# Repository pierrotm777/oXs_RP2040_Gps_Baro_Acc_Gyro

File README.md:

# oXs_RP2040_Gps_Baro_Acc_Gyro
 Multi Telemetry Protocols RP2040 Full version
 
## PCBWAY board link
You can find my shared pcb project [here](https://www.pcbway.com/project/shareproject/oXs_RP2040_Full_fdfb35e8.html).

 <object data="http://yoursite.com/the.pdf" type="application/pdf" width="700px" height="700px">
    <embed src="http://yoursite.com/the.pdf">
        <p>This browser does not support PDFs. Please download the PDF to view it: <a href="http://yoursite.com/the.pdf">Download PDF</a>.</p>
    </embed>
</object>

xfun::embed_file("homework.pdf")

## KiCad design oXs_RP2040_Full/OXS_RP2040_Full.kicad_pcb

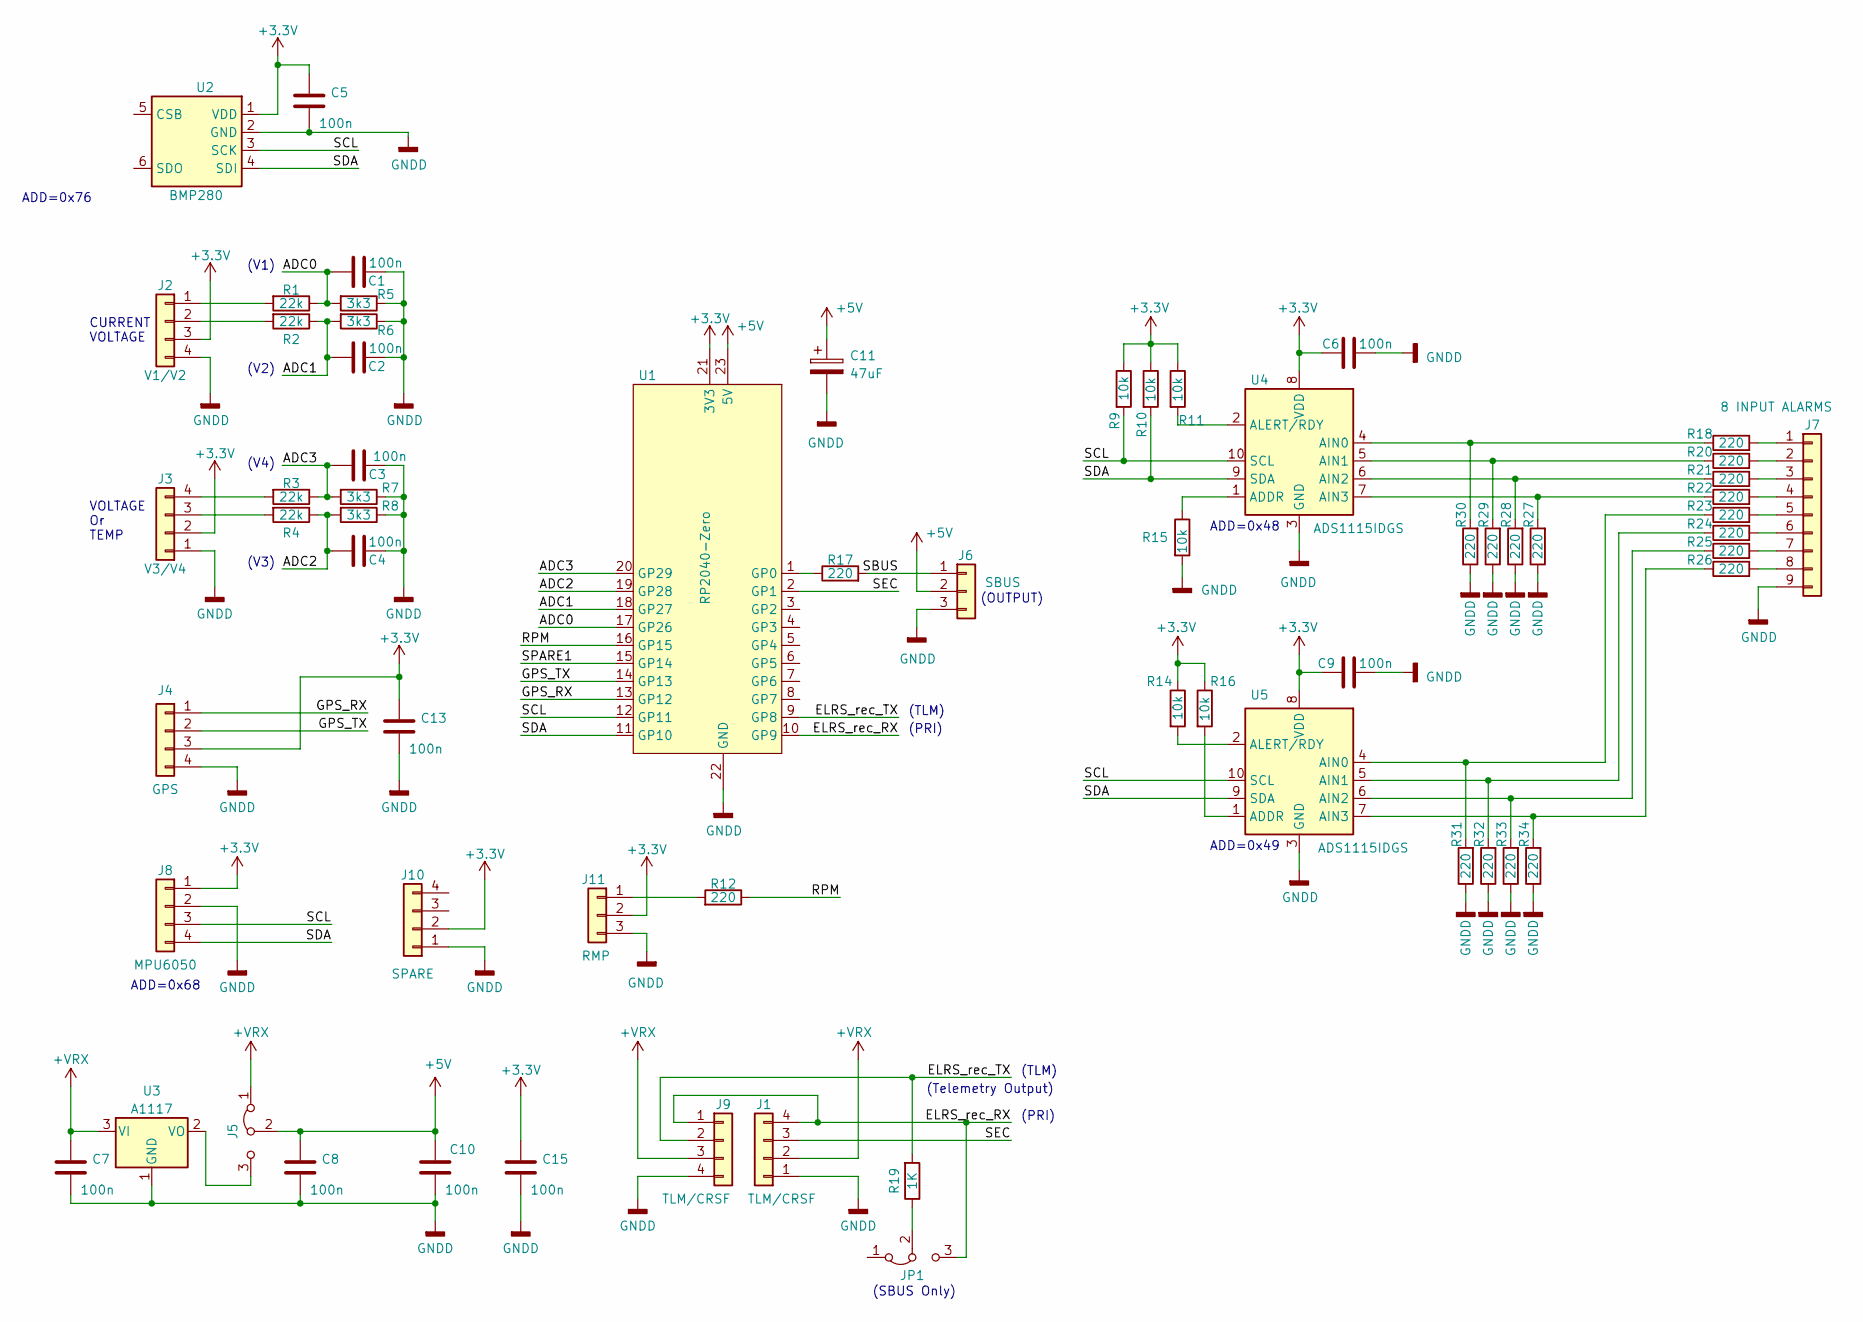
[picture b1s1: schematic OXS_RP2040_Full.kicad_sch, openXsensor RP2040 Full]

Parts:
C1, C2, C3, C4, C5, C6, C7, C8, C9, C10, C13, C15: 100n; C_1206_3216Metric_Pad1.33x1.80mm_HandSolder
C11: 47uF; CAPPM7343X310N
J1, J9: TLM/CRSF; PinHeader_1x04_P2.54mm_Horizontal_Mod
J2: V1/V2; PinHeader_1x04_P2.54mm_Horizontal_Mod
J3: V3/V4; PinHeader_1x04_P2.54mm_Horizontal_Mod
J4: GPS; PinHeader_1x04_P2.54mm_Horizontal_Mod
J5: SELECT_POWER; PinHeader_1x03_P2.54mm_Vertical
J6: SBUS; Pin_Header_Straight_1x03_Mod_Pitch2.54mm
J7: 8 INPUT ALARMS; JST_EH_B9B-EH-A_1x09_P2.50mm_Vertical
J8: MPU6050; PinHeader_1x04_P2.54mm_Vertical
J10: SPARE; PinHeader_1x04_P2.54mm_Horizontal_Mod
J11: RMP; Pin_Header_Straight_1x03_Mod_Pitch2.54mm
JP1: SBUS2; PinHeader_1x03_P2.54mm_Vertical
R1, R2, R3, R4: 22k; R_1206_3216Metric_Pad1.30x1.75mm_HandSolder
R5, R6, R7, R8: 3k3; R_1206_3216Metric_Pad1.30x1.75mm_HandSolder
R9, R10, R11, R14, R15, R16: 10k; R_1206_3216Metric_Pad1.30x1.75mm_HandSolder
R12, R17, R18, R20, R21, R22, R23, R24, R25, R26, R27, R28, R29, R30, R31, R32, R33, R34: 220; R_1206_3216Metric_Pad1.30x1.75mm_HandSolder
R19: 1K; R_1206_3216Metric_Pad1.30x1.75mm_HandSolder
U1: RP2040-Zero
U2: BMP280
U3: A1117; SOT-223-3_TabPin2
U4, U5: ADS1115IDGS; TSSOP-10_3x3mm_P0.5mm

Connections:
+3.3V: C5.1, C6.2, C9.2, C13.1, C15.1, J2.3, J3.2, J4.3, J8.1, J10.2, J11.2, R9.1, R10.1, R11.1, R14.1, R16.1, U1.21 (3V3), U2.1 (VDD), U4.8 (VDD), U5.8 (VDD)
+5V: C8.1, C10.1, C11.1, J5.2 (C), J6.2, U1.23 (5V)
+VRX: C7.1, J1.2, J5.1 (A), J9.3, U3.3 (VI)
/ADC0: C1.2, R1.1, R5.2, U1.17 (GP26)
/ADC1: C2.2, R2.1, R6.2, U1.18 (GP27)
/ADC2: C4.2, R4.1, R8.2, U1.19 (GP28)
/ADC3: C3.2, R3.1, R7.2, U1.20 (GP29)
/ELRS_rec_RX: J1.4, J9.1, JP1.3 (B), U1.10 (GP9)
/ELRS_rec_TX: J9.2, R19.2, U1.9 (GP8)
/GPS_RX: J4.1, U1.13 (GP12)
/GPS_TX: J4.2, U1.14 (GP13)
/RPM: R12.1, U1.16 (GP15)
/SBUS: J6.1, R17.2
/SCL: J8.3, R9.2, U1.12 (GP11), U2.3 (SCK), U4.10 (SCL), U5.10 (SCL)
/SDA: J8.4, R10.2, U1.11 (GP10), U2.4 (SDI), U4.9 (SDA), U5.9 (SDA)
/SEC: J1.3, U1.2 (GP1)
/SPARE1: U1.15 (GP14)
GNDD: C1.1, C2.1, C3.1, C4.1, C5.2, C6.1, C7.2, C8.2, C9.1, C10.2, C11.2, C13.2, C15.2, J1.1, J2.4, J3.1, J4.4, J6.3, J7.9, J8.2, J9.4, J10.1, J11.3, R5.1, R6.1, R7.1, R8.1, R15.2, R27.1, R28.1, R29.1, R30.1, R31.1, R32.1, R33.1, R34.1, U1.22 (GND), U2.2 (GND), U3.1 (GND), U4.3 (GND), U5.3 (GND)
unnamed: J2.1, R1.2
unnamed: J2.2, R2.2
unnamed: J3.3, R4.2
unnamed: J3.4, R3.2
unnamed: J5.3 (B), U3.2 (VO)
unnamed: J7.1, R18.2
unnamed: J7.2, R20.2
unnamed: J7.3, R21.2
unnamed: J7.4, R22.2
unnamed: J7.5, R23.2
unnamed: J7.6, R24.2
unnamed: J7.7, R25.2
unnamed: J7.8, R26.2
unnamed: J11.1, R12.2
unnamed: JP1.2 (C), R19.1
unnamed: R17.1, U1.1 (GP0)
unnamed: R15.1, U4.1 (ADDR)
unnamed: R18.1, R30.2, U4.4 (AIN0)
unnamed: R20.1, R29.2, U4.5 (AIN1)
unnamed: R21.1, R28.2, U4.6 (AIN2)
unnamed: R22.1, R27.2, U4.7 (AIN3)
unnamed: R11.2, U4.2 (ALERT/RDY)
unnamed: R16.2, U5.1 (ADDR)
unnamed: R23.1, R31.2, U5.4 (AIN0)
unnamed: R24.1, R32.2, U5.5 (AIN1)
unnamed: R25.1, R33.2, U5.6 (AIN2)
unnamed: R26.1, R34.2, U5.7 (AIN3)
unnamed: R14.2, U5.2 (ALERT/RDY)

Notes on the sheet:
CURRENT VOLTAGE
(SBUS Only)
(V4)
ADD=0x49
(TLM)
(PRI)
(V2)
VOLTAGE Or TEMP
(OUTPUT)
(V1)
ADD=0x48
(Telemetry Output)
ADD=0x76
(V3)
ADD=0x68

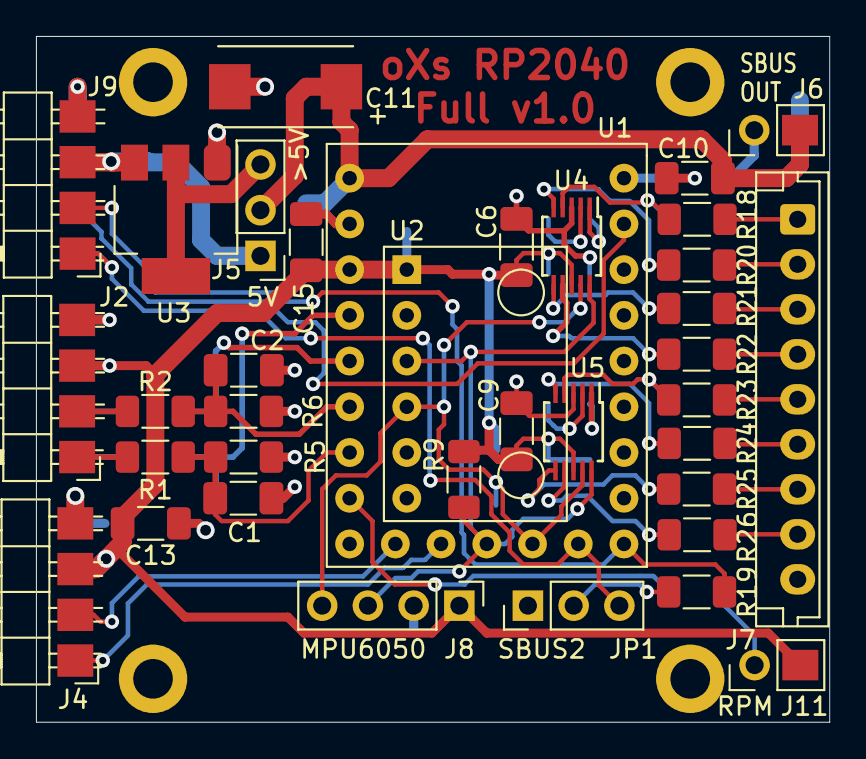
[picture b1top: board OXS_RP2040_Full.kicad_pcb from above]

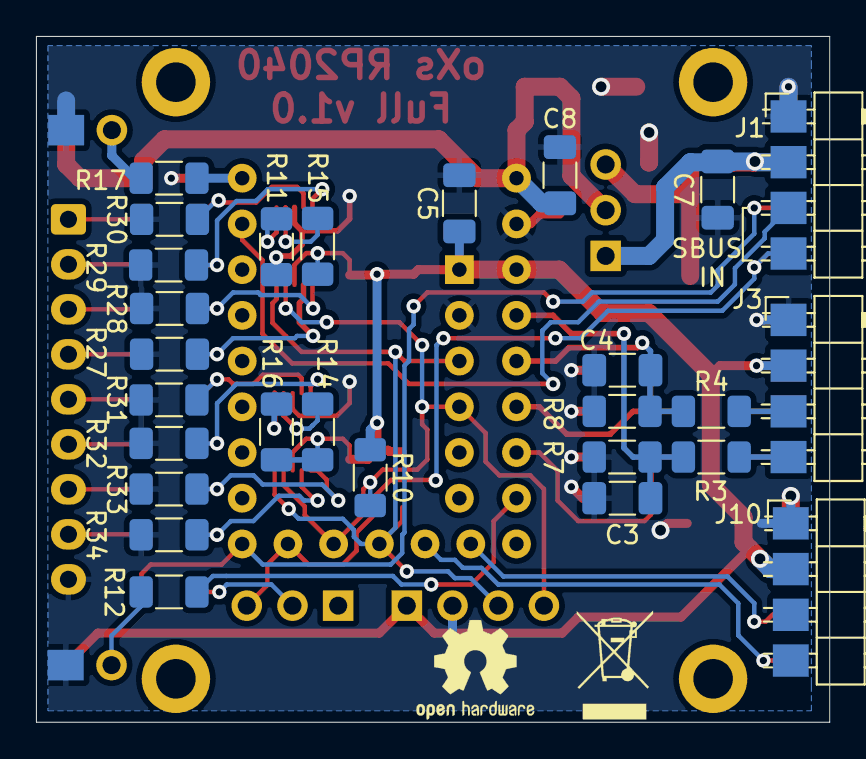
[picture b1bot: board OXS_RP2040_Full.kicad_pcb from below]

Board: 2 copper layers, 44.1 x 38.1 mm, 63 parts (27 on the bottom side), 45 nets.

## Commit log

2023-03-28 Add Kicad files & Gerber
2023-04-02 replace mpu6050 connection
2023-04-02 little adds
2023-04-05 update / build gerber
2023-04-27 Add documentation file
2023-04-27 mise à jour doc oXs
2023-04-27 mise à jour images
2023-04-28 Mise à jour doc
2023-04-29 add Termite config
2023-04-30 Add Voltages, current and Rpm sensors
2023-05-01 Update current sensor
2023-05-03 Update terminal config page
2023-05-05 Add PWM outputs
2023-05-09 Add mini doc Frsky
2023-05-09 Add Sbus2, Jeti mini doc
2023-05-09 Add Hott mini doc
2023-05-11 Add ELRS protocol documentation
2023-05-11 swap rx tx elrs docs
2023-05-12 Add SRXL2, update ELRS
2023-05-15 Add config telemetry for each protocol
2023-09-21 Add how to build oxs board
2023-09-21 update pictures
2023-11-29 Add all documentations
2024-03-30 archive v1.1
2024-03-30 Add V1.2
2024-03-30 Update v1.2
    move connectors for a 2.54mm space
2024-03-30 upadate
    add R before transistor base
2024-04-09 Add pictures and readme file
2025-05-26 add Flysky doc
2025-05-26 add pictures
2025-05-26 rename kicad files
